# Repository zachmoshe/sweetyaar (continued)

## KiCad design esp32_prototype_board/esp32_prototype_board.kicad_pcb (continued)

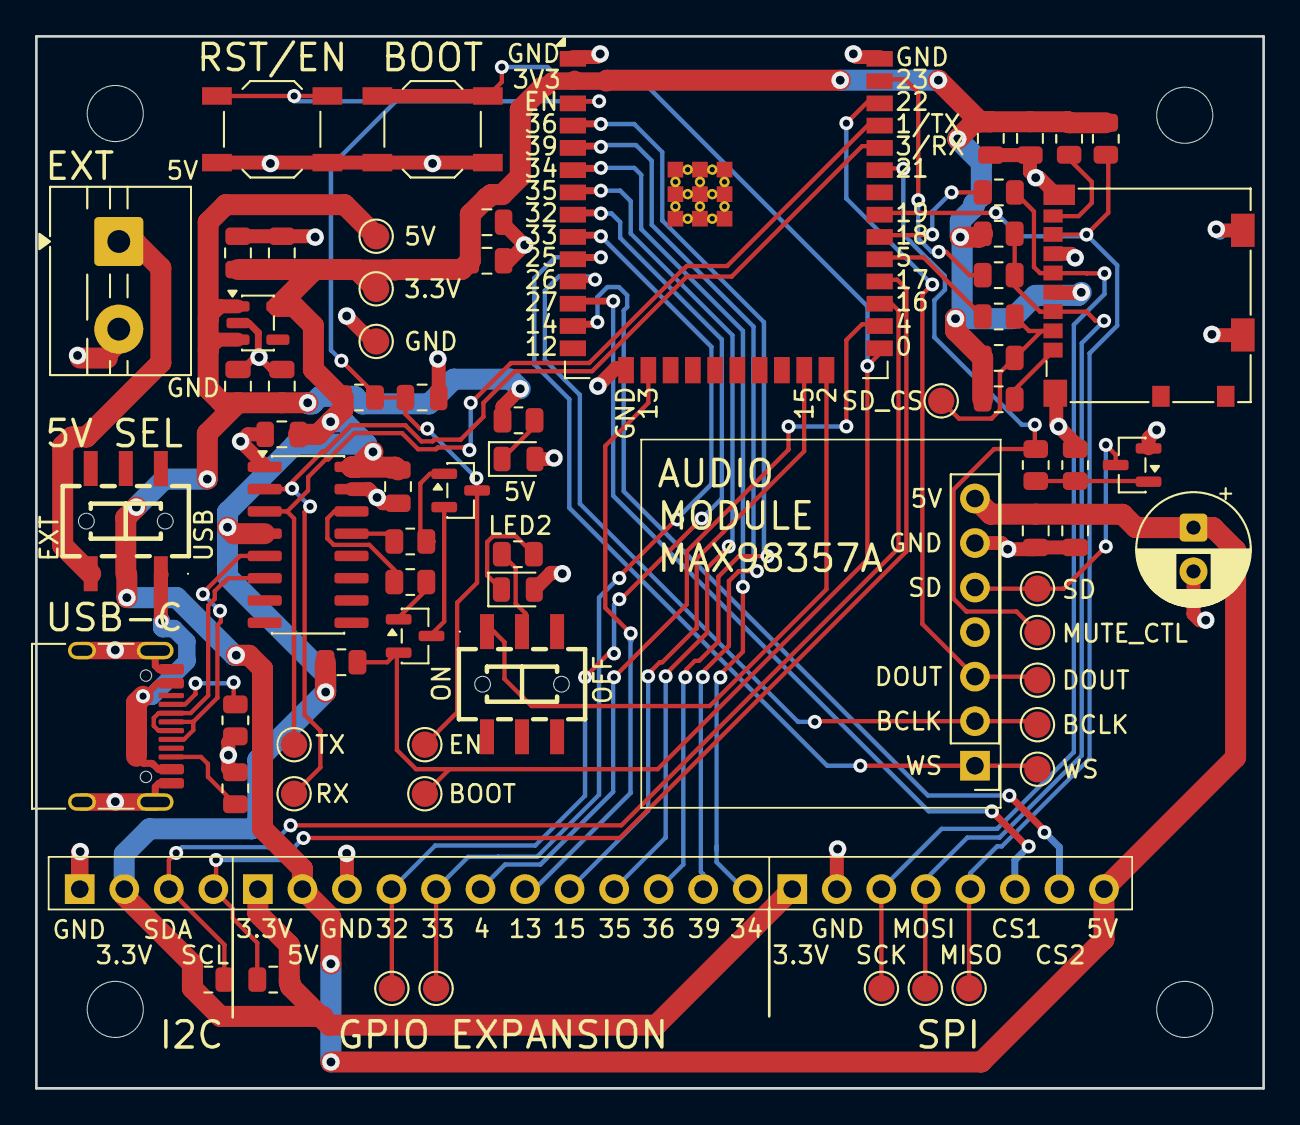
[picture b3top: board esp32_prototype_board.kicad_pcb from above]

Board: 4 copper layers, 70.0 x 60.0 mm, 75 parts (0 on the bottom side), 50 nets.

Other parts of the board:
C14: 100nF; C_0805_2012Metric
H1, H2, H3, H4: M3 mounting hole; MountingHole_3.2mm_M3
JP2: GPIO2 LED SW; SW-SMD_MS-22D28-G020

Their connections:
/5V_SYS: C14.1; also elsewhere on the board
/GND: C14.2; also elsewhere on the board
/GPIO2_LED: JP2.1 (A1); also elsewhere on the board
/LED_STATUS_IN: JP2.2 (COM1); also elsewhere on the board

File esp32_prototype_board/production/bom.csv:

Designator,Footprint,Quantity,Value,LCSC Part #
"C1, C2, C7",0805,3,22uF,
"C10, C13, C14, C3, C4, C5, C8",0805,7,100nF,
"C12, C9",0805,2,10uF,
C6,0805,1,1uF,
D1,0805,1,5V PWR,
D2,0805,1,STATUS,
J1,USB_C_Receptacle_HRO_TYPE-C-31-M-12,1,USB-C USB2 sink,
J2,TerminalBlock_MaiXu_MX126-5.0-02P_1x02_P5.00mm,1,EXT 5V IN,
J4,microSD_HC_Molex_104031-0811,1,microSD SPI,
J6,PinHeader_1x08_P2.54mm_Vertical,1,SPI EXP,
J7,PinHeader_1x04_P2.54mm_Vertical,1,I2C EXP,
J8,PinHeader_1x12_P2.54mm_Vertical,1,GPIO EXP,
JP1,SW-SMD_MS-22D28-G020,1,5V source switch,
JP2,SW-SMD_MS-22D28-G020,1,GPIO2 LED SW,
"Q1, Q2",SOT-23,2,SS8050/MMBT3904,
Q3,SOT-23,1,MMBT3904,
"R1, R2",0805,2,5.1k,
R10,0805,1,1k,
"R11, R12, R13",0805,3,22R,
"R14, R15, R16, R17, R18, R24, R4, R5, R6, R7",0805,10,10k,
"R19, R20",0805,2,4.7k,
R25,0805,1,100k,
R3,0805,1,2.2k,
SW1,SW_SPST_TL3342,1,EN/RST,
SW2,SW_SPST_TL3342,1,BOOT,
TP1,TestPoint_Pad_D1.5mm,1,5V_SYS,
TP10,TestPoint_Pad_D1.5mm,1,SD_SCK,
TP11,TestPoint_Pad_D1.5mm,1,SD_MOSI,
TP12,TestPoint_Pad_D1.5mm,1,SD_MISO,
TP13,TestPoint_Pad_D1.5mm,1,SD_CS,
TP14,TestPoint_Pad_D1.5mm,1,I2S_BCLK,
TP15,TestPoint_Pad_D1.5mm,1,I2S_WS,
TP16,TestPoint_Pad_D1.5mm,1,I2S_DOUT,
TP17,TestPoint_Pad_D1.5mm,1,AMP_MUTE_CTL,
TP18,TestPoint_Pad_D1.5mm,1,AMP_SD_MODE,
TP2,TestPoint_Pad_D1.5mm,1,3V3,
TP3,TestPoint_Pad_D1.5mm,1,GND,
TP4,TestPoint_Pad_D1.5mm,1,EN,
TP5,TestPoint_Pad_D1.5mm,1,BOOT,
TP6,TestPoint_Pad_D1.5mm,1,UART0_TX,
TP7,TestPoint_Pad_D1.5mm,1,UART0_RX,
TP8,TestPoint_Pad_D1.5mm,1,GPIO32,
TP9,TestPoint_Pad_D1.5mm,1,GPIO33,
U1,SOIC-16_3.9x9.9mm_P1.27mm,1,CH340C,
U2,SOT-23-5,1,AP2112K-3.3,
U3,ESP32-WROOM-32E,1,ESP32-WROOM-32E,
U4,PinHeader_1x07_P2.54mm_Vertical,1,MAX98357A blue module,

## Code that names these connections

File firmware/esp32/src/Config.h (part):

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    SWEETYAAR_AMP_MUTE_ACTIVE_HIGH != 0;

// --- SD card (SPI) ----------------------------------------------------------
static constexpr int PIN_SD_SCK     = 18;
static constexpr int PIN_SD_MISO    = 19;
static constexpr int PIN_SD_MOSI    = 23;
static constexpr int PIN_SD_CS      = 5;
static constexpr uint32_t SD_SPI_FREQUENCY_HZ = 20000000;
// FatFs reserves about 4 KB per file slot even when no file is open, and the
// library default of 5 slots starved Bluetooth connection setup of heap. Playback
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static constexpr int PIN_BTN2       = 33;  // Button 2: Animals

// --- Sleep / power gating ---------------------------------------------------
static constexpr int PIN_VIB_WAKE   = 27;  // Externally biased NC vibration switch to GND; wake HIGH
static constexpr int PIN_PERIPH_PWR_EN = 13;  // SD, battery-sense, and 5 V shared enable

// Pulsed 5 V soft start. Held HIGH from the start, the TPS63802 charges the
// 470 uF C_AMP3 at its full current limit and the battery current exceeds the
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static constexpr uint32_t PERIPH_5V_PRECHARGE_OFF_US = 1500;

// --- Battery / BQ25186 charger ---------------------------------------------
// GPIO34/35 are input-only and use external 10 kOhm pull-ups to 3V3_AON.
// GPIO4 drives the base of the external /CE pull-down transistor: HIGH turns
// the transistor on and enables charging. Its reset-default internal pulldown
// and the physical base pulldown keep charging off through reset and boot;
// the physical pulldown also keeps it off with an unpowered ESP32/open switch.
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#endif

static constexpr bool HAS_BQ25186 = SWEETYAAR_BQ25186_ENABLED != 0;
static constexpr int PIN_CHARGER_ENABLE = 4;
static constexpr int PIN_CHARGER_SDA    = 16;
static constexpr int PIN_CHARGER_SCL    = 17;
static constexpr int PIN_CHARGER_PG     = 34;
static constexpr int PIN_CHARGER_INT    = 35;
static constexpr int PIN_BATTERY_ADC   = 36;
static constexpr uint32_t BATTERY_DIVIDER_TOP_OHMS = 634000;
static constexpr uint32_t BATTERY_DIVIDER_BOTTOM_OHMS = 200000;

// --- Status LED -------------------------------------------------------------
// Production fallback: WS2812B-V6, 24-bit GRB, driven directly from GPIO2.
// Board-specific selections are explicit in platformio.ini. Inversion remains
// available for hardware with an inverting level shifter; neither current
// environment uses it.
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
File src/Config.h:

#pragma once

// ---------------------------------------------------------------------------
// SweetYaar — Hardware pin assignments & compile-time constants
// Target: ESP32-WROOM-32 + MAX98357A + SD card via SPI
// ---------------------------------------------------------------------------

// --- I2S (MAX98357A) --------------------------------------------------------
static constexpr int HW_I2S_BCLK    = 26;  // Bit clock
static constexpr int HW_I2S_WS      = 25;  // Word select / LRCK
static constexpr int HW_I2S_DOUT    = 22;  // Data out to MAX98357A DIN
static constexpr int PIN_AMP_MUTE   = 21;  // Rev A AMP_MUTE_CTL transistor input
static constexpr bool AMP_MUTE_ACTIVE_HIGH = true;  // HIGH pulls MAX98357A SD/MODE low

// --- SD card (SPI) ----------------------------------------------------------
static constexpr int PIN_SD_SCK     = 18;
static constexpr int PIN_SD_MISO    = 19;
static constexpr int PIN_SD_MOSI    = 23;
static constexpr int PIN_SD_CS      = 5;
static constexpr uint32_t SD_SPI_FREQUENCY_HZ = 20000000;

// --- Buttons (active LOW, internal pull-up) ---------------------------------
static constexpr int PIN_BTN1       = 32;  // Button 1: Songs
static constexpr int PIN_BTN2       = 33;  // Button 2: Animals

// --- Sleep / power gating ---------------------------------------------------
static constexpr int PIN_VIB_WAKE   = 27;  // Externally biased NC vibration switch to GND; wake HIGH
static constexpr int PIN_PERIPH_PWR_EN = 13;  // SD, battery-sense, and 5 V shared enable

// --- Battery / charger status ----------------------------------------------
// GPIO34/35 use external 10 kOhm pull-ups to 3V3_AON. GPIO36 reads the
// switched 820 kOhm / 300 kOhm BAT divider on ADC1_CH0.
static constexpr int PIN_CHARGER_STAT1 = 34;
static constexpr int PIN_CHARGER_STAT2 = 35;
static constexpr int PIN_BATTERY_ADC   = 36;
static constexpr uint32_t BATTERY_DIVIDER_TOP_OHMS = 820000;
static constexpr uint32_t BATTERY_DIVIDER_BOTTOM_OHMS = 300000;

// --- Status LED -------------------------------------------------------------
// Common-cathode RGB LED, driven active-HIGH by three LEDC PWM channels.
static constexpr int PIN_LED_RED    = 2;
static constexpr int PIN_LED_GREEN  = 16;
static constexpr int PIN_LED_BLUE   = 17;

// ---------------------------------------------------------------------------
// Timing constants
// ---------------------------------------------------------------------------
static constexpr uint32_t DEBOUNCE_MS          = 50;    // Button debounce window
static constexpr uint32_t BOTH_PRESS_WINDOW_MS = 100;   // Max gap for "both pressed"
static constexpr uint32_t KILLSWITCH_MS        = 10UL * 60UL * 1000UL;  // 10 minutes
static constexpr bool     DEFAULT_SLEEP_ENABLED = true;
static constexpr uint32_t SLEEP_NORMAL_IDLE_MS = 10UL * 60UL * 1000UL;
static constexpr uint32_t SLEEP_VIB_WAKE_IDLE_MS = 2UL * 60UL * 1000UL;
static constexpr uint32_t SLEEP_BLE_IDLE_MS = 2UL * 60UL * 1000UL;
static constexpr uint32_t BATTERY_SAMPLE_INTERVAL_MS = 30UL * 1000UL;
static constexpr uint32_t BATTERY_BOOT_SAMPLE_INTERVAL_MS = 100;
static constexpr uint8_t  BATTERY_BOOT_SAMPLE_COUNT = 5;
static constexpr uint8_t  BATTERY_ROLLING_SAMPLE_COUNT = 10;
static constexpr uint16_t BATTERY_GOOD_TO_MEDIUM_MV = 3400;
static constexpr uint16_t BATTERY_MEDIUM_TO_GOOD_MV = 3500;
static constexpr uint16_t BATTERY_MEDIUM_TO_LOW_MV = 3100;
static constexpr uint16_t BATTERY_LOW_TO_MEDIUM_MV = 3200;

// ---------------------------------------------------------------------------
// Audio
// ---------------------------------------------------------------------------
static constexpr int     SAMPLE_RATE        = 44100;
static constexpr int     CHANNELS           = 2;   // Stereo PCM; MAX98357A mixes to mono
static constexpr int     BITS_PER_SAMPLE    = 16;
static constexpr uint8_t DEFAULT_VOLUME_PCT = 75;  // Static default; SD config may override
static constexpr bool    DEFAULT_BEDTIME_ENABLED = true;
static constexpr uint16_t DEFAULT_BEDTIME_START_MINUTES = 18U * 60U + 30U;
static constexpr uint16_t DEFAULT_BEDTIME_END_MINUTES = 6U * 60U + 30U;
static constexpr uint8_t DEFAULT_BEDTIME_VOLUME_CAP_PCT = 45;
static constexpr int     BT_A2DP_RINGBUFFER_BYTES = 8 * 1024;
static constexpr int     BT_A2DP_I2S_TASK_STACK_BYTES = 2048;

// BLE parent controls are live session controls for local SD/WAV playback.
static constexpr bool ENABLE_BLE_PARENT_SERVICE = true;

// ---------------------------------------------------------------------------
// SD file paths
// ---------------------------------------------------------------------------
static constexpr char SD_CONFIG_FILE[] = "/config.json";
static constexpr char SONGS_ROOT[]    = "/songs";
static constexpr char ANIMALS_PATH[]  = "/animals";
static constexpr char METADATA_FILE[] = "metadata.json";
static constexpr char DEFAULT_THEME[] = "lullabies";
static constexpr char DEFAULT_BEDTIME_THEME[] = "lullabies";
static constexpr char ANIMALS_THEME_ID[] = "__animals";
static constexpr char ANIMALS_DISPLAY_NAME[] = "Animals";

// ---------------------------------------------------------------------------
// BLE UUIDs  (randomly generated, fixed per GATT schema version)
// ---------------------------------------------------------------------------
static constexpr char BLE_SERVICE_UUID[]    = "A1B2C3D4-E5F6-7890-ABCD-EF1234567890";
static constexpr char BLE_VOL_UUID[]        = "A1B2C3D4-E5F6-7890-ABCD-EF1234567891";
static constexpr char BLE_KILL_UUID[]       = "A1B2C3D4-E5F6-7890-ABCD-EF1234567892";
static constexpr char BLE_THEME_UUID[]      = "A1B2C3D4-E5F6-7890-ABCD-EF1234567893";
static constexpr char BLE_STATUS_UUID[]     = "A1B2C3D4-E5F6-7890-ABCD-EF1234567894";
static constexpr char BLE_THEMES_UUID[]     = "A1B2C3D4-E5F6-7890-ABCD-EF1234567895";
static constexpr char BLE_COMMAND_UUID[]    = "A1B2C3D4-E5F6-7890-ABCD-EF1234567896";
static constexpr char BLE_CONFIG_COMMAND_UUID[]  = "A1B2C3D4-E5F6-7890-ABCD-EF1234567897";
static constexpr char BLE_CONFIG_RESPONSE_UUID[] = "A1B2C3D4-E5F6-7890-ABCD-EF1234567898";
static constexpr char BLE_NOTICE_UUID[]          = "A1B2C3D4-E5F6-7890-ABCD-EF1234567899";
static constexpr char BLE_BATTERY_UUID[]         = "A1B2C3D4-E5F6-7890-ABCD-EF123456789A";
static constexpr size_t BLE_THEMES_MAX_BYTES = 512;
static constexpr int BLE_MAX_THEMES = 16;
static constexpr int BLE_CONFIG_THEME_PAGE_SIZE = 1;
static constexpr int BLE_CONFIG_SONG_PAGE_SIZE = 2;
static constexpr int CONFIG_MAX_DISABLED_THEMES = 64;
static constexpr int CONFIG_MAX_DISABLED_SONGS = 128;
static constexpr int CONFIG_SCAN_MAX_THEMES = 64;
static constexpr int CONFIG_SCAN_MAX_SONGS = 128;

// ---------------------------------------------------------------------------
// NVS namespace / keys
//
// Parent-editable toy settings live on the SD card. NVS is reserved for
// device-local settings that must survive SD-card replacement, stored as a
// compact JSON blob under NVS_KEY_DEVICE_CONFIG.
// ---------------------------------------------------------------------------
static constexpr char NVS_NAMESPACE[]         = "sweetyaar";
static constexpr char NVS_KEY_DEVICE_CONFIG[] = "device_config";

static constexpr char DEFAULT_BT_NAME[] = "SweetYaar";

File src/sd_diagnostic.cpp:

#include <Arduino.h>
#include <SPI.h>
#include <SD.h>

#include "Config.h"
#include "PeripheralPower.h"

static constexpr uint32_t SD_INIT_TEST_FREQ_HZ = 400000;
static constexpr uint32_t SD_STREAM_TEST_FREQ_HZ = 4000000;

static uint8_t waitForR1(uint16_t attempts = 32) {
    for (uint16_t i = 0; i < attempts; ++i) {
        uint8_t response = SPI.transfer(0xFF);
        if ((response & 0x80) == 0) {
            return response;
        }
    }
    return 0xFF;
}

static uint8_t sendSdCommand(uint8_t command,
                             uint32_t argument,
                             uint8_t crc,
                             uint8_t* extra = nullptr,
                             size_t extraLen = 0) {
    digitalWrite(PIN_SD_CS, LOW);
    SPI.transfer(0xFF);
    SPI.transfer(0x40 | command);
    SPI.transfer((argument >> 24) & 0xFF);
    SPI.transfer((argument >> 16) & 0xFF);
    SPI.transfer((argument >> 8) & 0xFF);
    SPI.transfer(argument & 0xFF);
    SPI.transfer(crc);

    uint8_t r1 = waitForR1();
    for (size_t i = 0; i < extraLen; ++i) {
        extra[i] = SPI.transfer(0xFF);
    }

    digitalWrite(PIN_SD_CS, HIGH);
    SPI.transfer(0xFF);
    return r1;
}

static void rawSpiProbe() {
    Serial.println("\n[Raw SPI probe]");
    SPI.beginTransaction(SPISettings(SD_INIT_TEST_FREQ_HZ, MSBFIRST, SPI_MODE0));

    digitalWrite(PIN_SD_CS, HIGH);
    Serial.printf("Idle levels before clocks: CS=%d MISO=%d\n",
                  digitalRead(PIN_SD_CS), digitalRead(PIN_SD_MISO));

    Serial.print("Idle SPI bytes with CS high:");
    for (int i = 0; i < 4; ++i) {
        Serial.printf(" %02X", SPI.transfer(0xFF));
    }
    Serial.println();

    for (int i = 0; i < 10; ++i) {
        SPI.transfer(0xFF);
    }

    uint8_t cmd0 = sendSdCommand(0, 0, 0x95);
    Serial.printf("CMD0 response: 0x%02X (expected 0x01 if the card hears us)\n", cmd0);

    uint8_t cmd8Extra[4] = {0};
    uint8_t cmd8 = sendSdCommand(8, 0x000001AA, 0x87, cmd8Extra, sizeof(cmd8Extra));
    Serial.printf("CMD8 response: 0x%02X, extra: %02X %02X %02X %02X\n",
                  cmd8, cmd8Extra[0], cmd8Extra[1], cmd8Extra[2], cmd8Extra[3]);

    if (cmd0 == 0x01 && cmd8 == 0x01) {
        Serial.println("Trying manual CMD55/ACMD41 init loop...");
        uint8_t cmd55 = 0xFF;
        uint8_t acmd41 = 0xFF;
        for (int attempt = 1; attempt <= 100; ++attempt) {
            cmd55 = sendSdCommand(55, 0, 0x01);
            acmd41 = sendSdCommand(41, 0x40000000, 0x01);
            if (attempt <= 5 || attempt % 10 == 0 || acmd41 == 0x00) {
                Serial.printf("  attempt %d: CMD55=0x%02X ACMD41=0x%02X\n",
                              attempt, cmd55, acmd41);
            }
            if (acmd41 == 0x00) {
                break;
            }
            delay(10);
        }

        if (acmd41 == 0x00) {
            uint8_t ocr[4] = {0};
            uint8_t cmd58 = sendSdCommand(58, 0, 0x01, ocr, sizeof(ocr));
            Serial.printf("Manual init OK. CMD58=0x%02X OCR: %02X %02X %02X %02X\n",
                          cmd58, ocr[0], ocr[1], ocr[2], ocr[3]);
        } else {
            Serial.printf("Manual init failed. Last CMD55=0x%02X ACMD41=0x%02X\n",
                          cmd55, acmd41);
        }
    }

    if (cmd0 == 0xFF) {
        Serial.println("No response at all. Suspect CS/SCK/MOSI/MISO wiring, module direction labels, or no card power.");
    } else if (cmd0 == 0x00) {
        Serial.println("MISO appears stuck LOW. Suspect MISO wiring, a short to GND, module/socket fault, or wrong module pin label.");
    } else if (cmd0 == 0x01) {
        Serial.println("Card responded to raw SPI. If SD.begin fails, the issue is likely library/module/card init compatibility.");
    } else {
        Serial.println("Card returned an unusual response; wiring may be partially working.");
    }

    SPI.endTransaction();
}

static bool arduinoSdProbe(uint32_t frequencyHz) {
    Serial.printf("\n[Arduino SD probe @ %lu Hz]\n", static_cast<unsigned long>(frequencyHz));
    Serial.println("Waiting 1000ms before SD.begin...");
    delay(1000);
    if (!SD.begin(PIN_SD_CS, SPI, frequencyHz)) {
        Serial.println("SD.begin failed");
        return false;
    }

    uint8_t cardType = SD.cardType();
    Serial.printf("cardType=%u\n", cardType);
    Serial.printf("cardSize=%llu MB\n", SD.cardSize() / (1024ULL * 1024ULL));

    File root = SD.open("/");
    if (!root) {
        Serial.println("Could not open root directory");
        SD.end();
        return false;
    }

    Serial.println("Root directory:");
    while (true) {
        File entry = root.openNextFile();
        if (!entry) {
            break;
        }
        Serial.printf("  %s%s %u bytes\n",
                      entry.name(),
                      entry.isDirectory() ? "/" : "",
                      static_cast<unsigned>(entry.size()));
        entry.close();
    }
    root.close();
    SD.end();
    return true;
}

static void holdOutput(const char* label, uint8_t pin, uint8_t level) {
    digitalWrite(pin, level);
    Serial.printf("  Measure SD %-3s -> GND now: expected about %.1fV for 8s\n",
                  label, level == HIGH ? 3.3 : 0.0);
    delay(8000);
}

static void slowLineProbe() {
    Serial.println("\n[Slow wiring probe]");
    Serial.println("Use DC volts, black probe on SD GND. Measure on the SD breakout's labeled pins.");
    Serial.println("This checks whether CS/CLK/DI actually arrive at the SD board.");

    SPI.end();
    pinMode(PIN_SD_CS, OUTPUT);
    pinMode(PIN_SD_SCK, OUTPUT);
    pinMode(PIN_SD_MOSI, OUTPUT);
    pinMode(PIN_SD_MISO, INPUT_PULLUP);

    digitalWrite(PIN_SD_CS, HIGH);
    digitalWrite(PIN_SD_SCK, LOW);
    digitalWrite(PIN_SD_MOSI, LOW);
    delay(500);

    holdOutput("CS", PIN_SD_CS, LOW);
    holdOutput("CS", PIN_SD_CS, HIGH);
    holdOutput("CLK", PIN_SD_SCK, LOW);
    holdOutput("CLK", PIN_SD_SCK, HIGH);
    holdOutput("DI", PIN_SD_MOSI, LOW);
    holdOutput("DI", PIN_SD_MOSI, HIGH);

    Serial.printf("  Measure SD DO  -> GND now: ESP32 pull-up reads %d; expected high-ish\n",
                  digitalRead(PIN_SD_MISO));
    delay(8000);
}

void setup() {
    Serial.begin(115200);
    delay(1000);

    Serial.println("\n=== SweetYaar SD Diagnostic ===");
    Serial.printf("Pins: CS=%d SCK=%d MISO=%d MOSI=%d\n",
                  PIN_SD_CS, PIN_SD_SCK, PIN_SD_MISO, PIN_SD_MOSI);
    Serial.println("Expected wiring: CS->GPIO5, SCK->GPIO18, MISO->GPIO19, MOSI->GPIO23");

    enablePeripheralPower();
    Serial.printf("[Power] Peripherals enabled on GPIO%d for SD diagnostic\n", PIN_PERIPH_EN);

    pinMode(PIN_SD_CS, OUTPUT);
    digitalWrite(PIN_SD_CS, HIGH);
    pinMode(PIN_SD_MISO, INPUT_PULLUP);
    delay(50);
    Serial.printf("GPIO pull-up probe before SPI.begin: MISO=%d\n", digitalRead(PIN_SD_MISO));

    SPI.begin(PIN_SD_SCK, PIN_SD_MISO, PIN_SD_MOSI, PIN_SD_CS);

    rawSpiProbe();
    arduinoSdProbe(SD_INIT_TEST_FREQ_HZ);
    delay(200);
    arduinoSdProbe(SD_STREAM_TEST_FREQ_HZ);
    slowLineProbe();

    Serial.println("\nDiagnostic complete. Press EN/RST to run again.");
}

void loop() {
    delay(1000);
}

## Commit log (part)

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2022-04-21 First working version with keyboard and web interfaces.
2022-04-21 adding controller stats
2022-04-21 adding random backgrounds
2022-04-21 adding startup and shutdown sounds
2022-04-21 binding WebInterface to port 80
2022-04-21 catching keyboardinterrupt on main_loop and exiting gracefully.
2022-04-23 terminating process before killing
2022-04-23 adding documentation on useful ffmpeg commands
2022-04-23 adding daytime/nighttime modes to the controller.
    controller is now in charge of choosing the random song to play.
2022-04-25 adding day_of_time override functionality and buttons
2022-04-25 adding reboot button
2022-04-25 switching to logrotate
2022-04-25 redirecting some output away from stderr/out
2022-04-25 adding the /stats HTTP GET command
2022-04-25 making top buttons smaller to fit a mobile screen
2022-04-26 fixing gitignore for DS_Store files
2022-04-28 starting sweetyaar on boot and rebooting if the main program exits.
2022-05-02 fixing rebooting issue in startup script
2022-05-02 adding the GPIO interface
2022-05-02 changing index.html to the new style
2022-05-05 new animals recordings
2022-05-05 new songs (daytime+nighttime)
2022-05-05 adding yaar photos
2022-05-05 changing gpio ports to solve some weird problem
2022-05-12 louder yaar callings
2022-08-06 deleted old code
2022-08-06 first version of sweeryaar2.0
2022-08-16 changing to sequential init + GPIO changes
2022-08-16 led_indicator bug fixes
2022-08-16 deleting main_old.py
2022-08-21 removing wifi from init
2022-08-21 removing code-workspace from git
2022-08-21 adding register_interfaces() to controller; changing audio callbacks
2022-08-23 adding daytime mode detection to audio_library
2022-08-23 minor changes
2022-08-23 adding kill_switch; moving actions constants to Actions class.
2022-08-23 move daytime mode management to the controller
2022-08-23 adding Bluetooth interface
2022-08-28 adding NeoPixel support to led_indicator
2022-09-08 adding commandline utilities
2022-09-08 adding a working BT interface + website
2022-09-09 changing images based on /images/metadata.json
2022-09-15 setting audio sample rate to 16000
2022-09-15 changing audio_player to have a constantly running loop.
2022-09-15 changing SPI init
2022-09-16 adding BTLogger
2022-09-16 preallocating the WAV file buffer before loading other stuff
2022-09-16 changing image refresh time
2022-09-16 fixing BT disconnecting
2022-09-16 fixing "no relative import" on micropython
2022-09-18 changing html page to have volume and battery meters
2022-09-18 adding indicate() context manager to LedIndicator
2022-09-18 adding SweetYaarDevice module; adding sleep after inactivity
2022-09-18 changing gpio pin to not collide with boot
2022-09-18 allowing some sleep time to broadcast logs when sleeping; minor fixes;
2022-09-18 removing ssl files from git
2022-09-20 adding recordings to .gitignore
2022-09-20 boosting CPU to 240M (smoother audio playing)
2022-09-20 adding BT physical switch
2022-09-20 changing default true-peak of WAVs to -6dB
2022-09-20 adding reset() to SweetYaarDevice; also getting rid of a duplicate commands mapping
2022-09-20 move bluetooth switch gpio to config file
2022-09-20 move controller error handling to the device
2022-09-26 adding bt_logger to audio_library
2022-09-26 adding volume control
2022-09-27 removing forgotten log..
2022-09-27 setting volume by the daytime mode
2022-09-27 performing cleanup even if going to REPL
2022-09-28 adding "--with-images" to upload_website.py
2022-09-28 cleaning up some JS code
2022-09-28 adding favicon
2022-09-29 converting all audio to 16KHz; also reducing CPU freq
2022-09-29 making the app PWA
2022-09-30 changing responsiveness of first row of buttons
2022-09-30 support new file formats and folder structure
2022-09-30 changing BT sweetyaar service UUID
2022-09-30 adding DEVICE_TIME_CHANGED event to controller
2022-10-02 change lightsleep to deepsleep
2022-10-08 Adding (real) battery monitoring
2022-10-08 change volume and battery meter UI
2022-10-10 changing meter color to --main-bg-color
2022-10-11 voltage calculation fix
2022-12-20 changing audio to 22050
2022-12-20 adding installation script on esp32; fixing typos in upload script
2022-12-21 supporting arbitrary playlists instead of daytime/nighttime only.
2022-12-24 memory stabilization fixes
2022-12-24 adding awake_pin
2022-12-24 fixing volume
2023-01-02 lowering base volume by 1 shift
2023-01-10 memory improvements
2023-02-12 changing I2S buffer size
2023-02-12 setting python version
2023-02-12 installing SweetYaar code as a frozen module in micropython
2023-02-12 bugfix - shouldn't sleep while playing a song. (for songs that are longer than `sleep_inactivity_threshold_secs`)
2023-02-26 removing BT switch check. BT is always active.
2023-02-26 changing random songs logic to a fixed permutation
2023-05-20 hotfix: audio_library bugs
2026-05-23 Initial SweetYaar working app
2026-05-24 Finalize star dust background
2026-05-25 Add initial PCB placement baseline
2026-05-26 Update app header artwork
2026-05-27 Minor UI changes
2026-05-29 Add config content curation
2026-06-02 Align docs with BLE content curation
2026-06-02 Add vibration sleep test target
2026-06-02 Add idle deep sleep mode
2026-06-02 Document sleep mode hardware and behavior
2026-06-02 Add sleep settings to parent app
2026-06-02 Fix sleep settings save payload
2026-06-02 Fix sleep config JSON parsing
2026-06-02 Polish settings controls layout
2026-06-03 adding final PCB files
2026-06-03 Add current codebase README
2026-06-04 moving esp32_dev board to a seperate project
2026-06-04 implementing regression and firmware tests
2026-06-04 docs: define bedtime mode
2026-06-05 firmware: implement bedtime mode runtime
2026-06-05 app: add bedtime mode controls
2026-06-05 tests: cover bedtime mode behavior
2026-06-05 Add parent app PWA support
    Add a manifest, service worker, install prompt, offline/update docs, and static PWA contract tests. Serialize initial Web Bluetooth reads so Android Chrome can connect reliably.
2026-06-05 Load parent app themes on connect
    Remove fallback theme labels from the remote picker and populate selectable themes from scanThemes during BLE connect, including the legacy config transport.
2026-06-05 Fix parent app icon alignment
    Resolve issue #11 by centering the volume icon asset, normalize settings toolbar button alignment on mobile, and bump the parent app cache.
2026-06-05 Polish parent app control alignment
    Center the volume icon across the full control block and replace the font back arrow with a fixed CSS chevron for mobile toolbar alignment.
2026-06-05 Use sliders icon for parent app settings
    Replace the main ready-screen gear glyph with a cached sliders SVG and keep the settings affordance aligned within the visible ready screen.
2026-06-05 app: polish bedtime ready controls
2026-06-05 firmware: keep bedtime active for theme overrides
2026-06-06 adding pyproject
2026-06-07 chaning app's icon/favicon
2026-06-07 adding the device's time in the main app
2026-06-07 Let the device sleep if BT is connected but paused
2026-06-13 setting AP2112K-3.3 as the chosen regulator
2026-06-27 reversing MUTE_AMP to support the dev board
2026-06-28 adding firmware support for load-switch configuration and controlling via GPIO13
